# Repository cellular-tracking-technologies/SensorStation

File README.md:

# SensorStation

This repo contains the SensorStation schematics and CAD files. You can use this to assist with development, troubleshoot problems, or even create your own SensorStation.

If you are looking to purchased a fully assembled and tested SensorStation, complete with Raspberry Pi Compute module installed, visit: http://store.celltracktech.com/

# SensorStation Overview

The SensorStation is a powerful platform for transmitting and receiving information wirelessly, with multiple radio channels.

While its primary function is to collect data from wildlife telemetry devices, it can be used for any multi-channel wireless
application, including IoT, amateur radio, and building wireless networks.

The SensorStation offers the following features:

* Support for the Raspberry Pi Compute Module CM3+ (pre-programmed with SensorGnome if purchased from CTT)
* USB OTG switch allows for programming of Compute Module while directly connected to board
* GPS receiver with built in chip antenna, with RF switch for external antennas
* 5 radio channels with SMA connectors featuring the HopeRF footprint, making it compatible with VHF and UHF systems, such as LoRa or FSK, from 142-1000MHz and 2.4GHz
* Each radio is controlled by a dedicated Atmel AVR 32U4, featuring the Arduino bootloader, hardwired to the USB network
* Raspberry Pi compatible header for connecting accessories, such as the InkyPhat eInk screen and more
* 4 directional buttons
* 2 status indication LEDs controlled by GPIO
* 3 I2C accessory ports, with dedicated GPIO per port
* Multi-channel ADC, for measuring system voltages, temperature, light levels, battery voltage, solar voltage, and additional channels broken out
* DS3231 real time clock with extreme accuracy along with coin cell slot
* Composite video output
* Wide range DC power input from 8-24VDC
* 6 USB 2.0 ports, each with dedicated transaction translator, typically used for Software Defined Radio (SDR)
* SIM800C quad band GSM modem
* eSIM (SIM on chip), soldered on if purchased from CTT (requires data plan)

# SensorStation Acessories

Also available for a variety of SensorStation accessories. You can even build your own. Check our our SensorStation Acessory Template to learn more.

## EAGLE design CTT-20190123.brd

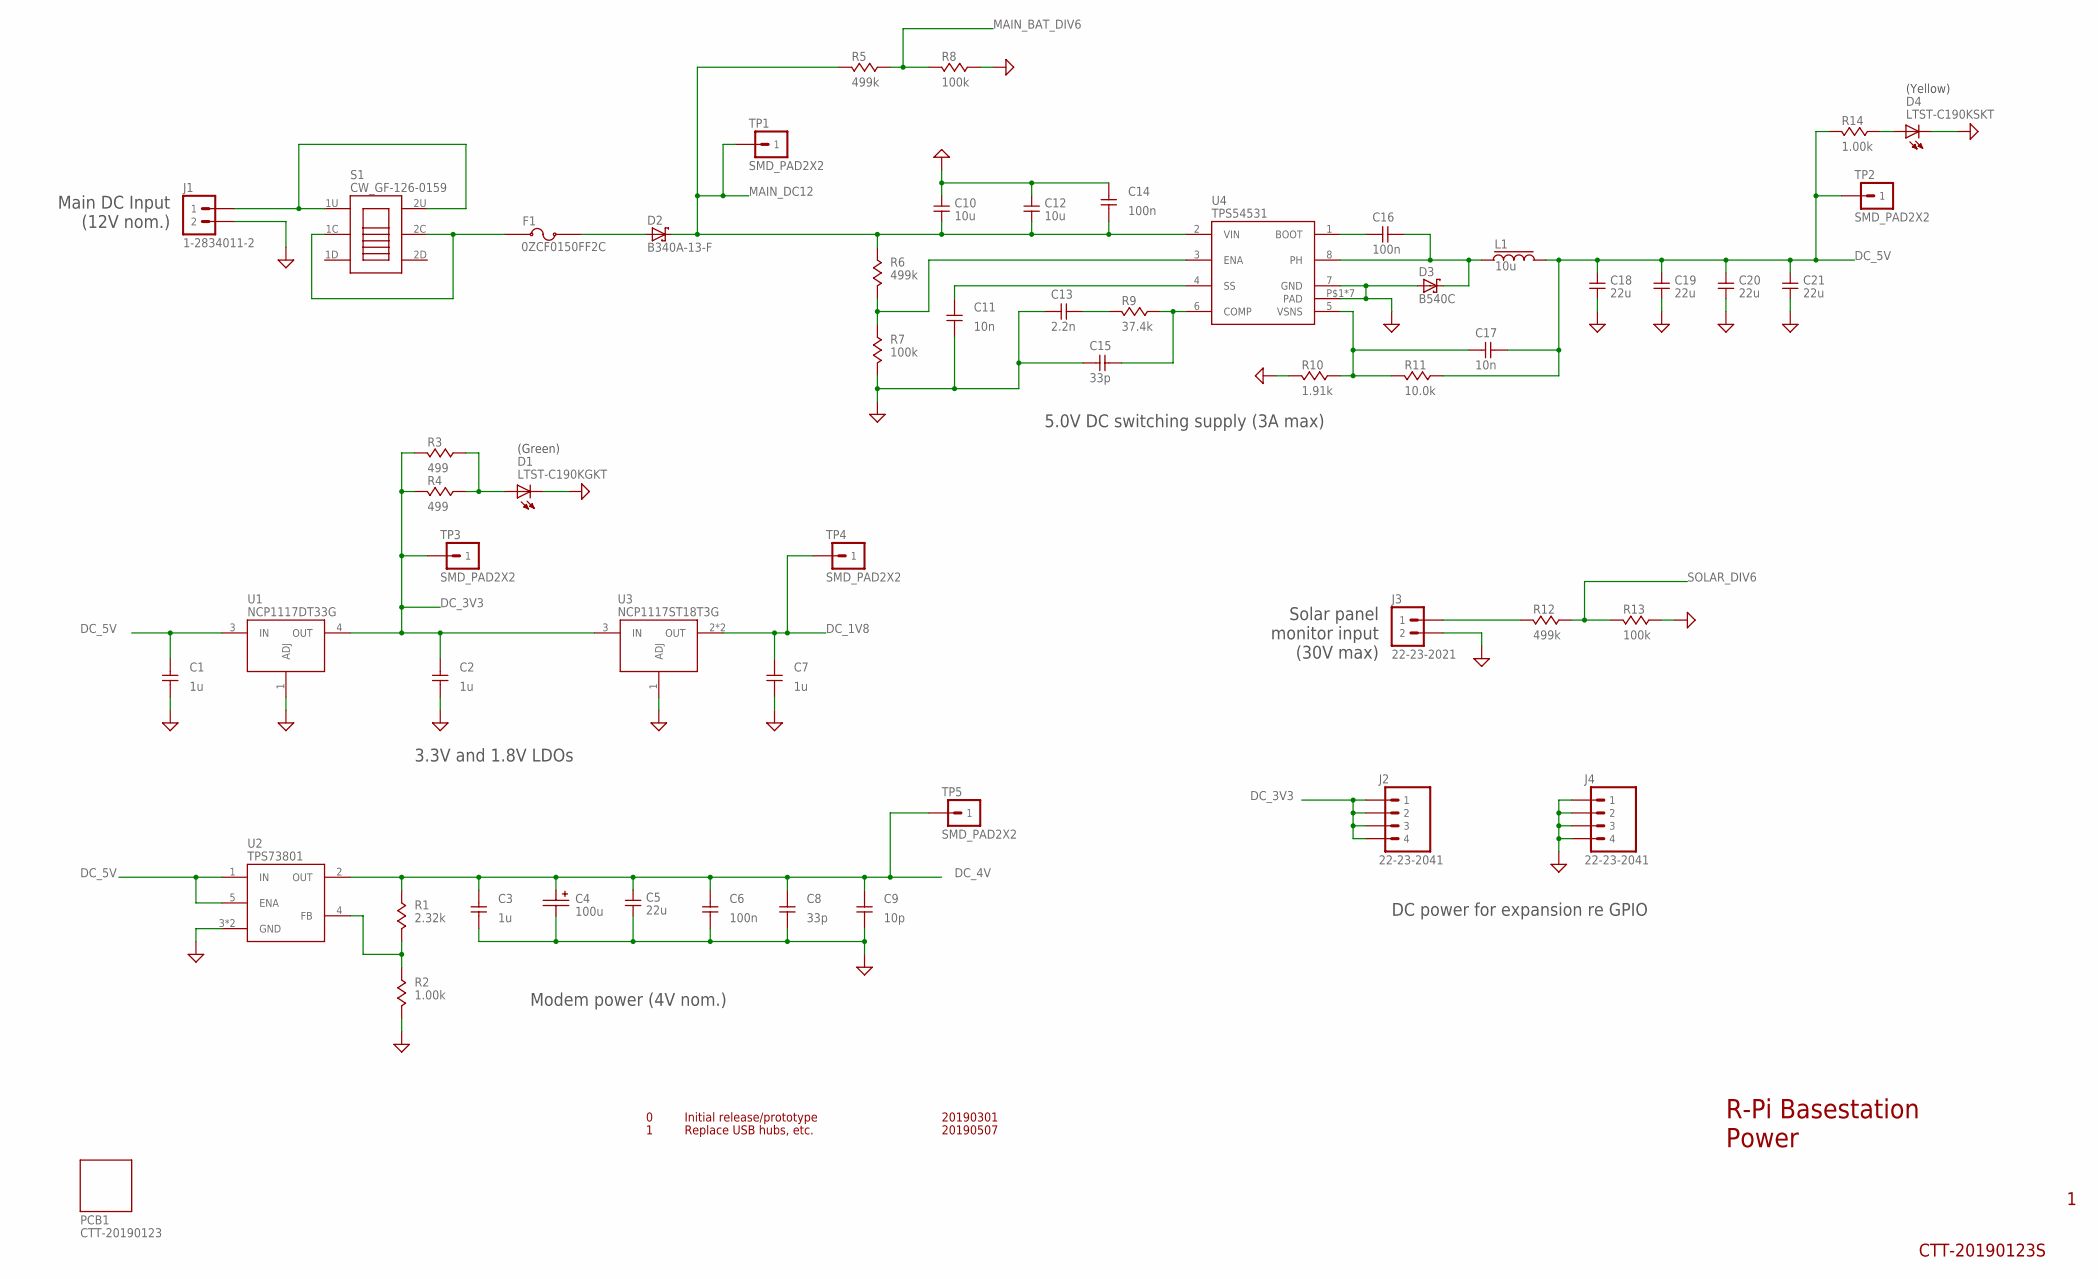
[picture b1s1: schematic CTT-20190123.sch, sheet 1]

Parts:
C1, C2, C3, C7: 1u; C0603_IPC7351_MED
C4: 100u; C7343
C5, C18, C19, C20, C21: 22u; C0805
C6, C14, C16: 100n; C0402_IPC7351_MED
C8, C15: 33p; C0402_IPC7351_MED
C9: 10p; C0402_IPC7351_MED
C10, C12: 10u; C0805
C11, C17: 10n; C0402_IPC7351_MED
C13: 2.2n; C0402_IPC7351_MED
D1: LTST-C190KGKT; LED0603
D2: B340A-13-F; SMA
D3: B540C; SMC
D4: LTST-C190KSKT; LED0603
F1: 0ZCF0150FF2C; SMD2920_0ZCF-SERIES
J1: 1-2834011-2
J2, J4: 22-23-2041; MTA100-4
J3: 22-23-2021; MTA100-2
L1: 10u; SRR1260
PCB1: CTT-20190123; BLANK_BRD
R1: 2.32k; R0402_IPC7351_MED
R2, R14: 1.00k; R0402_IPC7351_MED
R3, R4: 499; R0402_IPC7351_MED
R5, R6, R12: 499k; R0402_IPC7351_MED
R7, R8, R13: 100k; R0402_IPC7351_MED
R9: 37.4k; R0402_IPC7351_MED
R10: 1.91k; R0402_IPC7351_MED
R11: 10.0k; R0402_IPC7351_MED
S1: CW_GF-126-0159
TP1, TP2, TP3, TP4, TP5: SMD_PAD2X2; SMD_PAD
U1: NCP1117DT33G; DPAK
U2: TPS73801; TI_R-PDSO-G6
U3: NCP1117ST18T3G; SOT-223
U4: TPS54531; TI_R-PDSO-G8

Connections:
DC_1V8: C7.P$2 (2), TP4.1, U3.2 (OUT), U3.4 (OUT); also elsewhere on the board
DC_3V3: C2.P$2 (2), J2.1, J2.2, J2.3, J2.4, R3.P$2 (2), R4.P$2 (2), TP3.1, U1.4 (OUT), U3.3 (IN); also elsewhere on the board
DC_4V: C3.P$2 (2), C4.+ (POS), C5.2, C6.P$2 (2), C8.P$2 (2), C9.P$2 (2), R1.P$1 (1), TP5.1, U2.2 (OUT); also elsewhere on the board
DC_5V: C1.P$2 (2), C17.P$2 (2), C18.2, C19.2, C20.2, C21.2, L1.2, R11.P$1 (1), R14.P$2 (2), TP2.1, U1.3 (IN), U2.1 (IN), U2.5 (ENA); also elsewhere on the board
GND: C1.P$1 (1), C2.P$1 (1), C3.P$1 (1), C4.- (NEG), C5.1, C6.P$1 (1), C7.P$1 (1), C8.P$1 (1), C9.P$1 (1), C10.1, C11.P$1 (1), C12.1, C13.P$1 (1), C14.P$1 (1), C15.P$1 (1), C18.1, C19.1, C20.1, C21.1, D1.K, D3.A, D4.K, J1.2, J3.2, J4.1, J4.2, J4.3, J4.4, R2.P$2 (2), R7.P$2 (2), R8.P$1 (1), R10.P$2 (2), R13.P$1 (1), U1.1 (ADJ), U2.3 (GND), U2.TAB (GND), U3.1 (ADJ), U4.7 (GND), U4.P$1 (PAD), U4.P$2 (PAD), U4.P$3 (PAD), U4.P$4 (PAD), U4.P$5 (PAD), U4.P$6 (PAD), U4.PAD; also elsewhere on the board
MAIN_BAT_DIV6: R5.P$1 (1), R8.P$2 (2); also elsewhere on the board
MAIN_DC12: C10.2, C12.2, C14.P$2 (2), D2.C, R5.P$2 (2), R6.P$1 (1), TP1.1, U4.2 (VIN)
unnamed: C16.P$2 (2), D3.K (C), L1.P$1 (1), U4.8 (PH)
unnamed: R6.P$2 (2), R7.P$1 (1), U4.3 (ENA)
unnamed: C11.P$2 (2), U4.4 (SS)
unnamed: C16.P$1 (1), U4.1 (BOOT)
unnamed: C15.P$2 (2), R9.P$1 (1), U4.6 (COMP)
unnamed: C17.P$1 (1), R10.P$1 (1), R11.P$2 (2), U4.5 (VSNS)
unnamed: C13.P$2 (2), R9.P$2 (2)
unnamed: J1.1, S1.1U, S1.2U
unnamed: D2.A, F1.P$2
unnamed: D4.A, R14.P$1 (1)
unnamed: D1.A, R3.P$1 (1), R4.P$1 (1)
unnamed: R1.P$2 (2), R2.P$1 (1), U2.4 (FB)
unnamed: J3.1, R12.P$2 (2)
unnamed: F1.P$1, S1.1C, S1.2C
SOLAR_DIV6: R12.P$1 (1), R13.P$2 (2); also elsewhere on the board

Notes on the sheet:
Main DC Input (12V nom.)
Modem power (4V nom.)
Solar panel monitor input (30V max)
5.0V DC switching supply (3A max)
3.3V and 1.8V LDOs
DC power for expansion re GPIO
R-Pi Basestation Power
CTT-20190123S
(Yellow)
(Green)
20190507
Initial release/prototype
Replace USB hubs, etc.
20190301

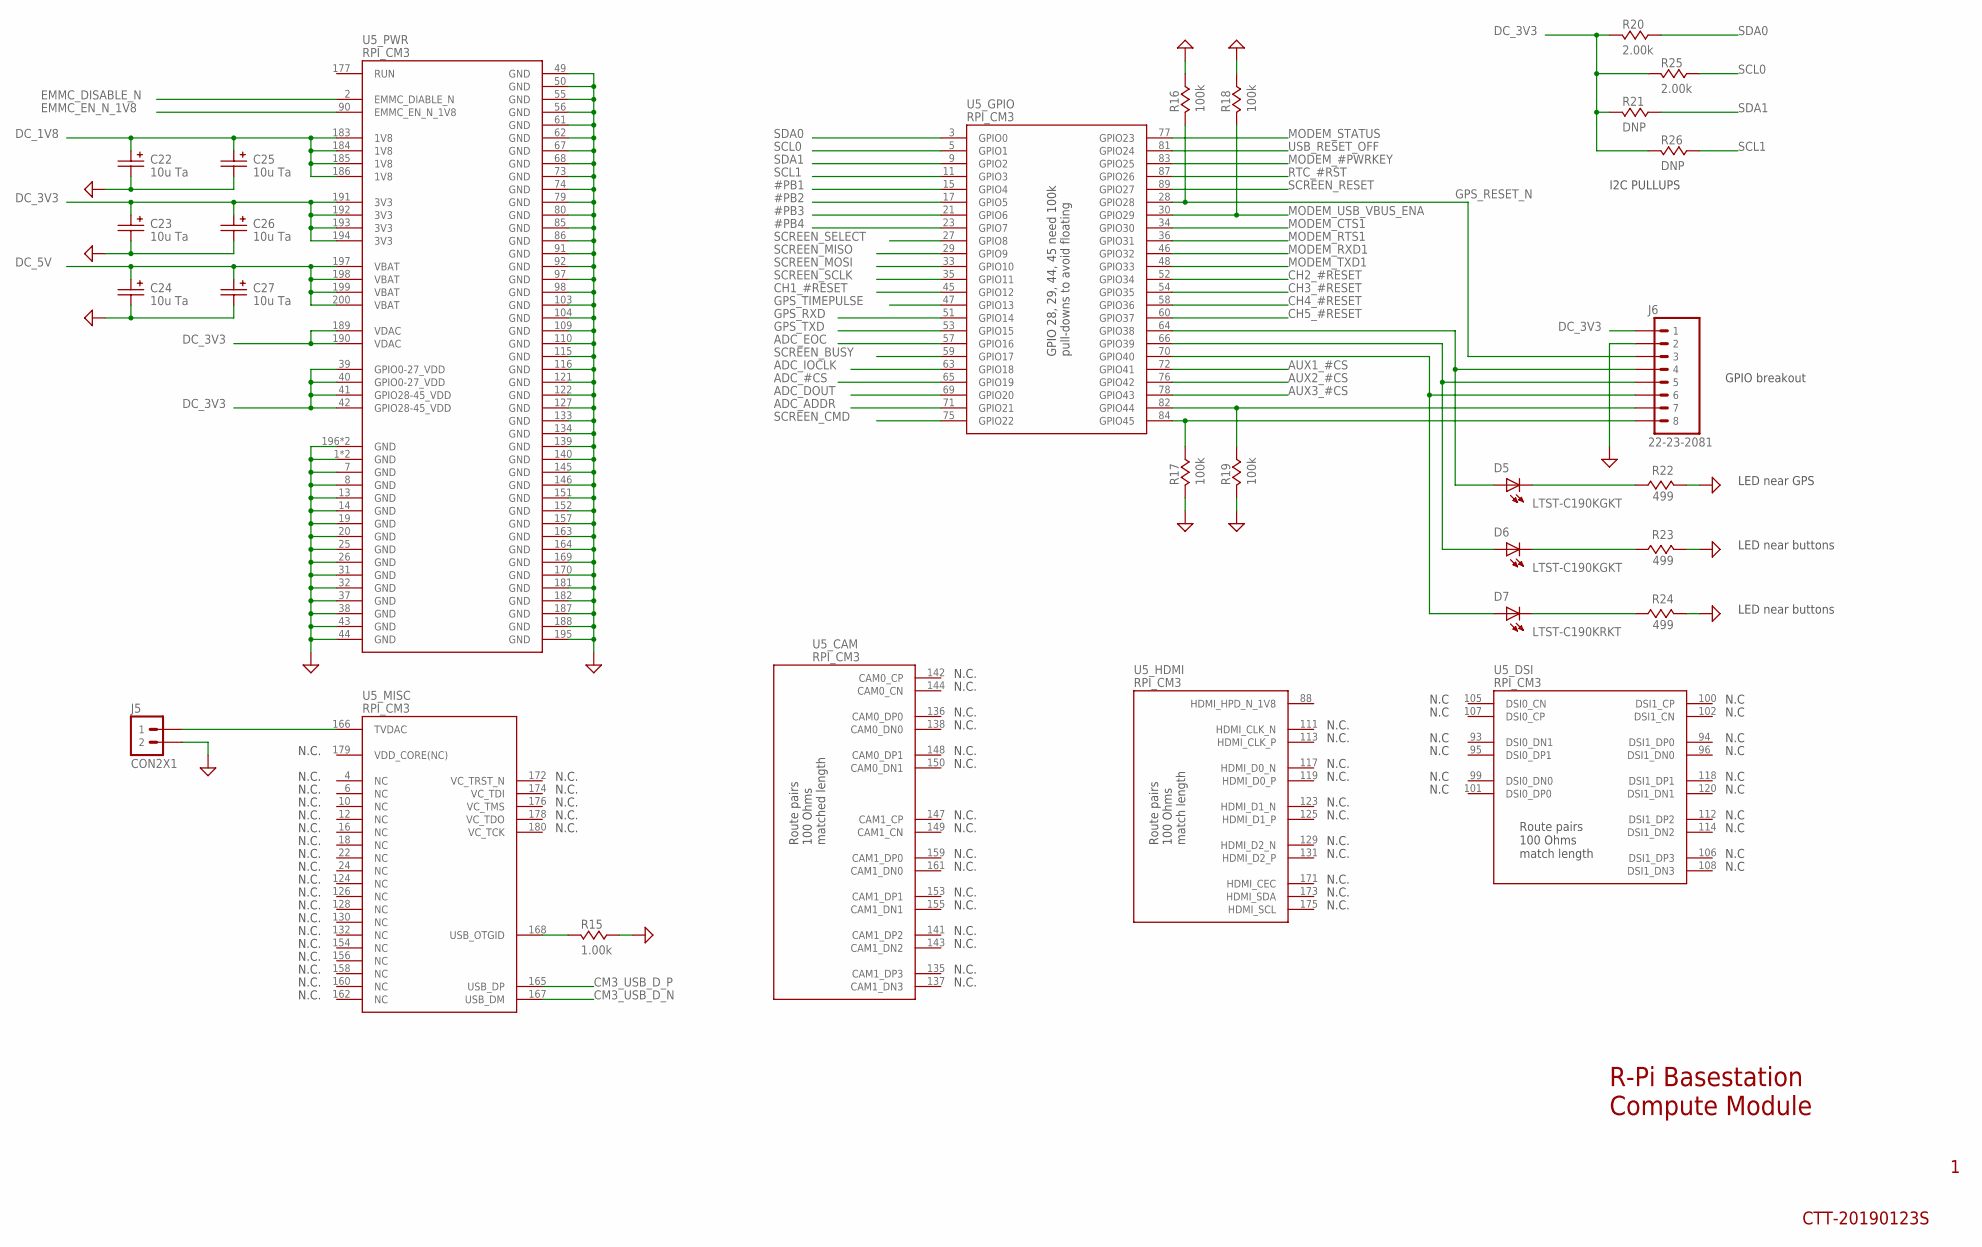
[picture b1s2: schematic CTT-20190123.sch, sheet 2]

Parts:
C22, C23, C24, C25, C26, C27: 10u Ta; CAP1411-AVX_F97SERIES
D5, D6: LTST-C190KGKT; LED0603
D7: LTST-C190KRKT; LED0603
J5: CON2X1
J6: 22-23-2081; MTA100-8
R15: 1.00k; R0402_IPC7351_MED
R16, R17, R18, R19: 100k; R0402_IPC7351_MED
R20, R25: 2.00k; R0402_IPC7351_MED
R21, R26: DNP; R0402_IPC7351_MED
R22, R23, R24: 499; R0402_IPC7351_MED
U5: RPI_CM3; 1473149-4

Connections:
#PB1: U5.15 (GPIO4); also elsewhere on the board
#PB2: U5.17 (GPIO5); also elsewhere on the board
#PB3: U5.21 (GPIO6); also elsewhere on the board
#PB4: U5.23 (GPIO7); also elsewhere on the board
ADC_#CS: U5.65 (GPIO19); also elsewhere on the board
ADC_ADDR: U5.71 (GPIO21); also elsewhere on the board
ADC_DOUT: U5.69 (GPIO20); also elsewhere on the board
ADC_EOC: U5.57 (GPIO16); also elsewhere on the board
ADC_IOCLK: U5.63 (GPIO18); also elsewhere on the board
AUX1_#CS: U5.72 (GPIO41); also elsewhere on the board
AUX2_#CS: U5.76 (GPIO42); also elsewhere on the board
AUX3_#CS: U5.78 (GPIO43); also elsewhere on the board
CH1_#RESET: U5.45 (GPIO12); also elsewhere on the board
CH2_#RESET: U5.52 (GPIO34); also elsewhere on the board
CH3_#RESET: U5.54 (GPIO35); also elsewhere on the board
CH4_#RESET: U5.58 (GPIO36); also elsewhere on the board
CH5_#RESET: U5.60 (GPIO37); also elsewhere on the board
CM3_USB_D_N: U5.167 (USB_DM); also elsewhere on the board
CM3_USB_D_P: U5.165 (USB_DP); also elsewhere on the board
DC_1V8: C22.+ (POS), C25.+ (POS), U5.183 (1V8), U5.184 (1V8), U5.185 (1V8), U5.186 (1V8); also elsewhere on the board
DC_3V3: C23.+ (POS), C26.+ (POS), J6.1, R20.P$2 (2), R21.P$2 (2), R25.P$2 (2), R26.P$2 (2), U5.39 (GPIO0-27_VDD), U5.40 (GPIO0-27_VDD), U5.41 (GPIO28-45_VDD), U5.42 (GPIO28-45_VDD), U5.189 (VDAC), U5.190 (VDAC), U5.191 (3V3), U5.192 (3V3), U5.193 (3V3), U5.194 (3V3); also elsewhere on the board
DC_5V: C24.+ (POS), C27.+ (POS), U5.197 (VBAT), U5.198 (VBAT), U5.199 (VBAT), U5.200 (VBAT); also elsewhere on the board
EMMC_DISABLE_N: U5.2 (EMMC_DIABLE_N); also elsewhere on the board
EMMC_EN_N_1V8: U5.90 (EMMC_EN_N_1V8); also elsewhere on the board
GND: C22.- (NEG), C23.- (NEG), C24.- (NEG), C25.- (NEG), C26.- (NEG), C27.- (NEG), J5.2, J6.2, R15.P$1 (1), R16.P$1 (1), R17.P$2 (2), R18.P$1 (1), R19.P$2 (2), R22.P$2 (2), R23.P$2 (2), R24.P$2 (2), U5.1 (GND), U5.7 (GND), U5.8 (GND), U5.13 (GND), U5.14 (GND), U5.19 (GND), U5.20 (GND), U5.25 (GND), U5.26 (GND), U5.31 (GND), U5.32 (GND), U5.37 (GND), U5.38 (GND), U5.43 (GND), U5.44 (GND), U5.49 (GND), U5.50 (GND), U5.55 (GND), U5.56 (GND), U5.61 (GND), U5.62 (GND), U5.67 (GND), U5.68 (GND), U5.73 (GND), U5.74 (GND), U5.79 (GND), U5.80 (GND), U5.85 (GND), U5.86 (GND), U5.91 (GND), U5.92 (GND), U5.97 (GND), U5.98 (GND), U5.103 (GND), U5.104 (GND), U5.109 (GND), U5.110 (GND), U5.115 (GND), U5.116 (GND), U5.121 (GND), U5.122 (GND), U5.127 (GND), U5.133 (GND), U5.134 (GND), U5.139 (GND), U5.140 (GND), U5.145 (GND), U5.146 (GND), U5.151 (GND), U5.152 (GND), U5.157 (GND), U5.163 (GND), U5.164 (GND), U5.169 (GND), U5.170 (GND), U5.181 (GND), U5.182 (GND), U5.187 (GND), U5.188 (GND), U5.195 (GND), U5.196 (GND), U5.P$1 (GND), U5.P$2 (GND); also elsewhere on the board
GPS_RESET_N: J6.3, R16.P$2 (2), U5.28 (GPIO28); also elsewhere on the board
GPS_RXD: U5.51 (GPIO14); also elsewhere on the board
GPS_TIMEPULSE: U5.47 (GPIO13); also elsewhere on the board
GPS_TXD: U5.53 (GPIO15); also elsewhere on the board
MODEM_#PWRKEY: U5.83 (GPIO25); also elsewhere on the board
MODEM_CTS1: U5.34 (GPIO30); also elsewhere on the board
MODEM_RTS1: U5.36 (GPIO31); also elsewhere on the board
MODEM_RXD1: U5.46 (GPIO32); also elsewhere on the board
MODEM_STATUS: U5.77 (GPIO23); also elsewhere on the board
MODEM_TXD1: U5.48 (GPIO33); also elsewhere on the board
MODEM_USB_VBUS_ENA: R18.P$2 (2), U5.30 (GPIO29); also elsewhere on the board
unnamed: J5.1, U5.166 (TVDAC)
unnamed: R15.P$2 (2), U5.168 (USB_OTGID)
unnamed: J6.8, R17.P$1 (1), U5.84 (GPIO45)
unnamed: J6.7, R19.P$1 (1), U5.82 (GPIO44)
unnamed: D5.A, J6.4, U5.64 (GPIO38)
unnamed: D6.A, J6.5, U5.66 (GPIO39)
unnamed: D7.A, J6.6, U5.70 (GPIO40)
unnamed: D6.K, R23.P$1 (1)
unnamed: D7.K, R24.P$1 (1)
unnamed: D5.K, R22.P$1 (1)
RTC_#RST: U5.87 (GPIO26); also elsewhere on the board
SCL0: R25.P$1 (1), U5.5 (GPIO1); also elsewhere on the board
SCL1: R26.P$1 (1), U5.11 (GPIO3); also elsewhere on the board
SCREEN_BUSY: U5.59 (GPIO17); also elsewhere on the board
SCREEN_CMD: U5.75 (GPIO22); also elsewhere on the board
SCREEN_MISO: U5.29 (GPIO9); also elsewhere on the board
SCREEN_MOSI: U5.33 (GPIO10); also elsewhere on the board
SCREEN_RESET: U5.89 (GPIO27); also elsewhere on the board
SCREEN_SCLK: U5.35 (GPIO11); also elsewhere on the board
SCREEN_SELECT: U5.27 (GPIO8); also elsewhere on the board
SDA0: R20.P$1 (1), U5.3 (GPIO0); also elsewhere on the board
SDA1: R21.P$1 (1), U5.9 (GPIO2); also elsewhere on the board
USB_RESET_OFF: U5.81 (GPIO24); also elsewhere on the board

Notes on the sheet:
N.C.
N.C
I2C PULLUPS
R-Pi Basestation Compute Module
CTT-20190123S
GPIO breakout
LED near GPS
LED near buttons

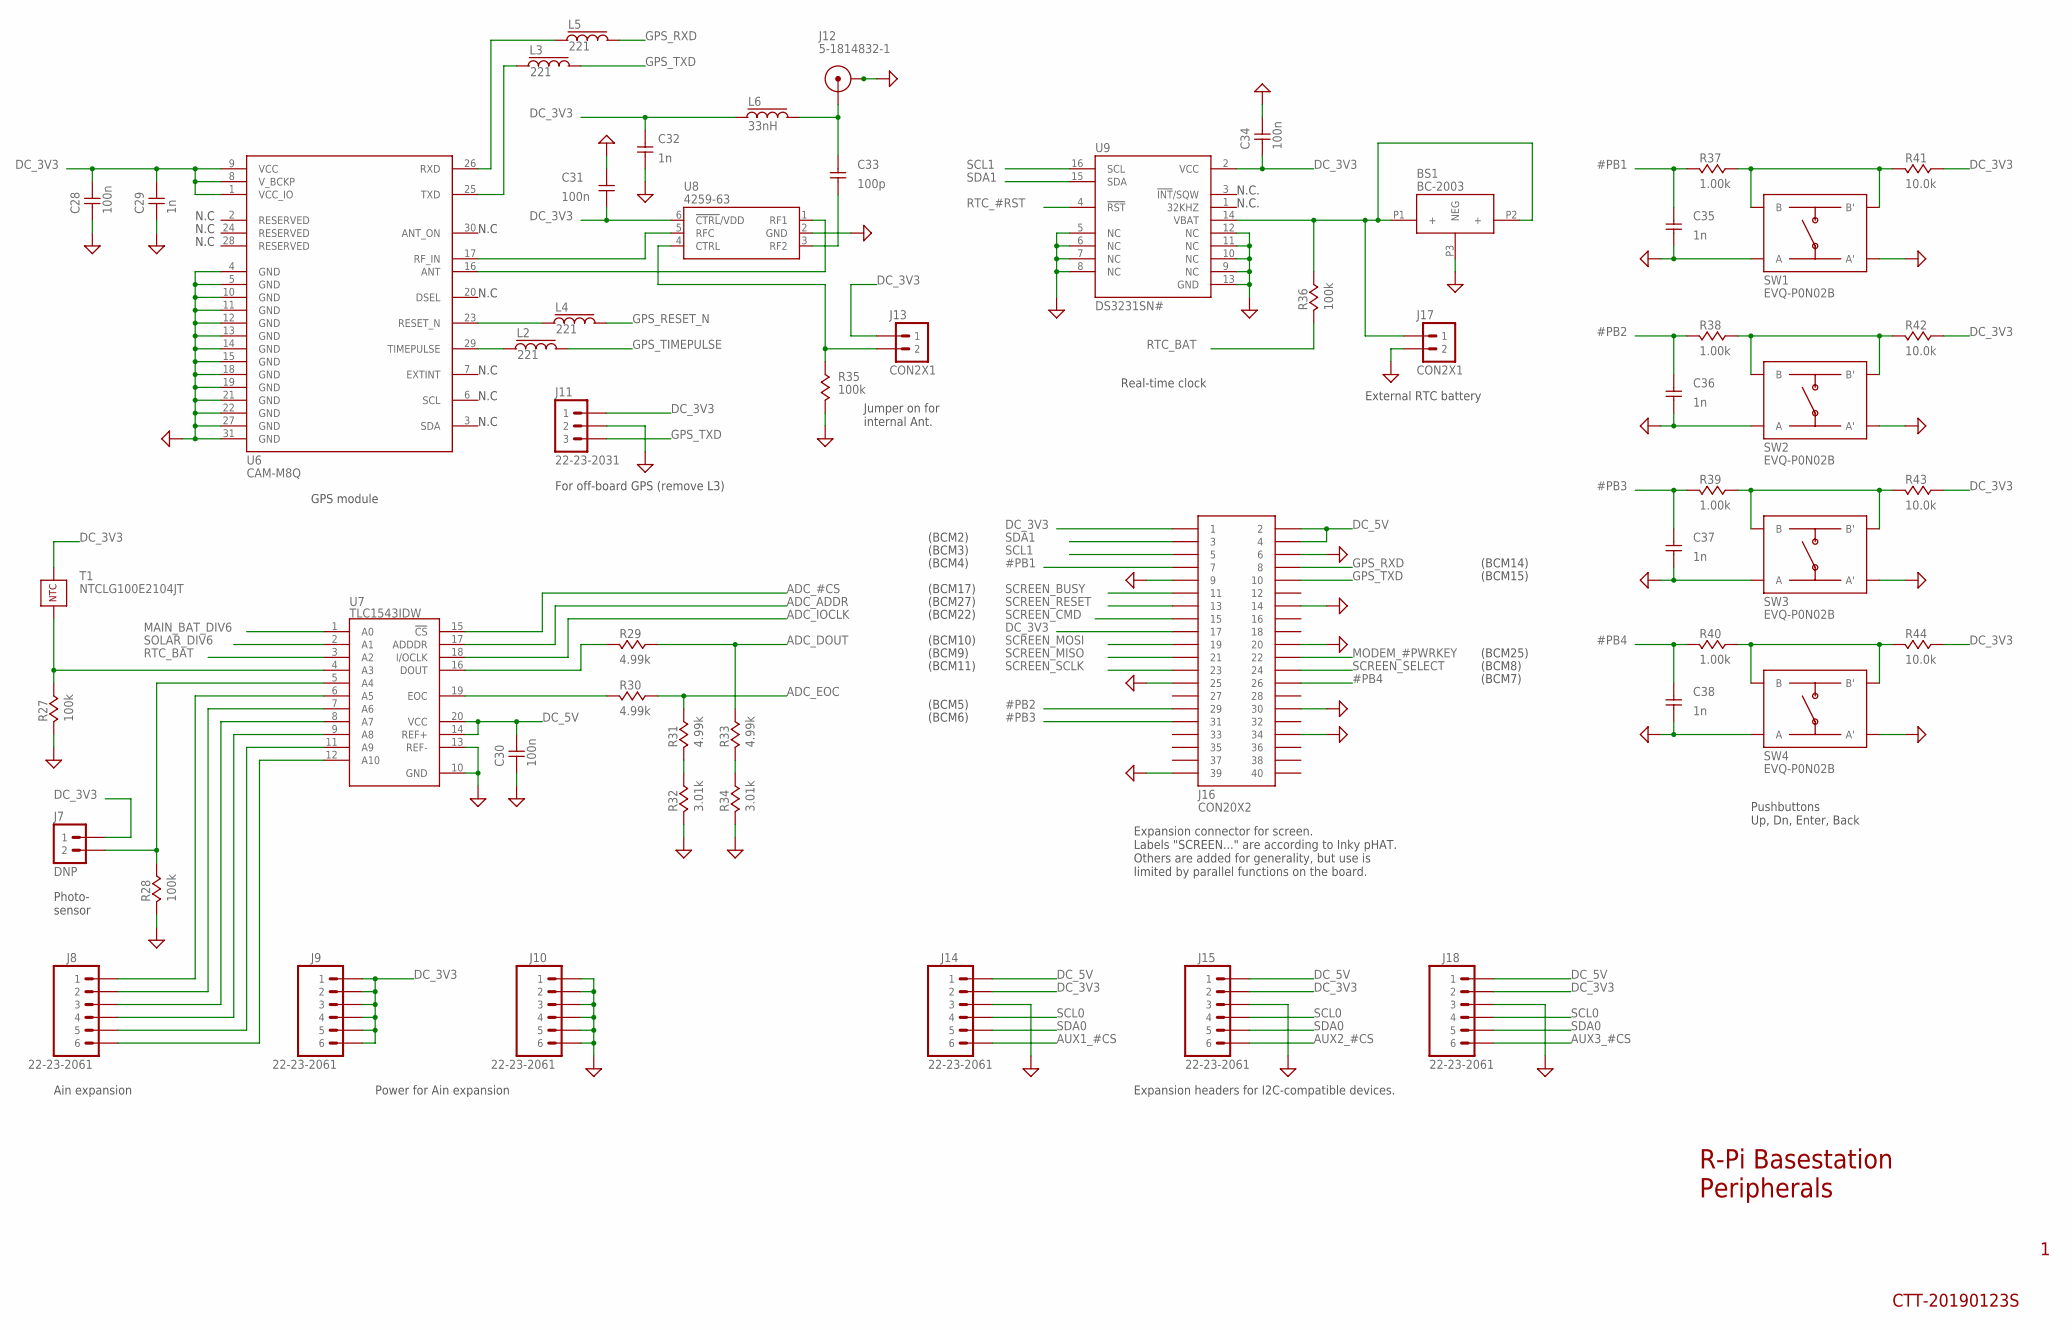
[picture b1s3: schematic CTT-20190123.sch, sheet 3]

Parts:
BS1: BC-2003; BC-2003-TR
C28, C30, C31, C34: 100n; C0402_IPC7351_MED
C29, C32, C35, C36, C37, C38: 1n; C0402_IPC7351_MED
C33: 100p; C0402_IPC7351_MED
J7: DNP; CON2X1
J8, J9, J10, J14, J15, J18: 22-23-2061; MTA100-6
J11: 22-23-2031; MTA100-3
J12: 5-1814832-1; CON_SMA_TH_VERT
J13, J17: CON2X1
J16: CON20X2
L2, L3, L4, L5: 221; L0402_IPC7351_MED
L6: 33nH; L0402_IPC7351_MED
R27, R28, R35, R36: 100k; R0402_IPC7351_MED
R29, R30, R31, R33: 4.99k; R0402_IPC7351_MED
R32, R34: 3.01k; R0402_IPC7351_MED
R37, R38, R39, R40: 1.00k; R0402_IPC7351_MED
R41, R42, R43, R44: 10.0k; R0402_IPC7351_MED
SW1, SW2, SW3, SW4: EVQ-P0N02B; EVQP0
T1: NTCLG100E2104JT; DO35-VERT
U6: CAM-M8Q; LCC31
U7: TLC1543IDW; SOIC20_DW0020A
U8: 4259-63; SC-70_PEREGRINE
U9: DS3231SN#; SO16-WIDE_MAXIM

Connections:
#PB1: C35.P$2 (2), J16.7, R37.P$2 (2); also elsewhere on the board
#PB2: C36.P$2 (2), J16.29, R38.P$2 (2); also elsewhere on the board
#PB3: C37.P$2 (2), J16.31, R39.P$2 (2); also elsewhere on the board
#PB4: C38.P$2 (2), J16.26, R40.P$2 (2); also elsewhere on the board
ADC_#CS: U7.15 (!CS); also elsewhere on the board
ADC_ADDR: U7.17 (ADDDR); also elsewhere on the board
ADC_DOUT: R29.P$1 (1), R33.P$1 (1); also elsewhere on the board
ADC_EOC: R30.P$1 (1), R31.P$1 (1); also elsewhere on the board
ADC_IOCLK: U7.18 (I/OCLK); also elsewhere on the board
AUX1_#CS: J14.6; also elsewhere on the board
AUX2_#CS: J15.6; also elsewhere on the board
AUX3_#CS: J18.6; also elsewhere on the board
DC_3V3: C28.P$2 (2), C29.P$2 (2), C31.P$1 (1), C32.P$2 (2), C34.P$1 (1), J7.1, J9.1, J9.2, J9.3, J9.4, J9.5, J9.6, J11.1, J13.1, J14.2, J15.2, J16.1, J16.17, J18.2, L6.P$1 (1), R41.P$1 (1), R42.P$1 (1), R43.P$1 (1), R44.P$1 (1), T1.P$1 (1), U6.1 (VCC_IO), U6.8 (V_BCKP), U6.9 (VCC), U8.6 (!CTRL!/VDD), U9.2 (VCC); also elsewhere on the board
DC_5V: C30.P$2 (2), J14.1, J15.1, J16.2, J16.4, J18.1, U7.14 (REF+), U7.20 (VCC); also elsewhere on the board
GND: BS1.P3 (NEG), C28.P$1 (1), C29.P$1 (1), C30.P$1 (1), C31.P$2 (2), C32.P$1 (1), C34.P$2 (2), C35.P$1 (1), C36.P$1 (1), C37.P$1 (1), C38.P$1 (1), J10.1, J10.2, J10.3, J10.4, J10.5, J10.6, J11.2, J12.P$1 (GND), J12.P$2 (GND), J12.P$3 (GND), J12.P$4 (GND), J14.3, J15.3, J16.6, J16.9, J16.14, J16.20, J16.25, J16.30, J16.34, J16.39, J17.2, J18.3, R27.P$2 (2), R28.P$2 (2), R32.P$2 (2), R34.P$2 (2), R35.P$2 (2), SW1.A, SW1.A@1 (A'), SW2.A, SW2.A@1 (A'), SW3.A, SW3.A@1 (A'), SW4.A, SW4.A@1 (A'), U6.4 (GND), U6.5 (GND), U6.10 (GND), U6.11 (GND), U6.12 (GND), U6.13 (GND), U6.14 (GND), U6.15 (GND), U6.18 (GND), U6.19 (GND), U6.21 (GND), U6.22 (GND), U6.27 (GND), U6.31 (GND), U7.10 (GND), U7.13 (REF-), U8.2 (GND), U9.5 (NC), U9.6 (NC), U9.7 (NC), U9.8 (NC), U9.9 (NC), U9.10 (NC), U9.11 (NC), U9.12 (NC), U9.13 (GND); also elsewhere on the board
GPS_RESET_N: L4.P$2 (2); also elsewhere on the board
GPS_RXD: J16.8, L5.P$2 (2); also elsewhere on the board
GPS_TIMEPULSE: L2.P$2 (2); also elsewhere on the board
GPS_TXD: J11.3, J16.10, L3.P$2 (2); also elsewhere on the board
MAIN_BAT_DIV6: U7.1 (A0); also elsewhere on the board
MODEM_#PWRKEY: J16.22; also elsewhere on the board
unnamed: C33.P$2 (2), J12.C (SIG), L6.P$2 (2)
unnamed: U6.17 (RF_IN), U8.5 (RFC)
unnamed: C33.P$1 (1), U8.3 (RF2)
unnamed: U6.16 (ANT), U8.1 (RF1)
unnamed: L4.P$1 (1), U6.23 (RESET_N)
unnamed: L5.P$1 (1), U6.26 (RXD)
unnamed: L3.P$1 (1), U6.25 (TXD)
unnamed: L2.P$1 (1), U6.29 (TIMEPULSE)
unnamed: BS1.P1 (+), BS1.P2 (+), J17.1, R36.P$1 (1), U9.14 (VBAT)
unnamed: R30.P$2 (2), U7.19 (EOC)
unnamed: R29.P$2 (2), U7.16 (DOUT)
unnamed: J7.2, R28.P$1 (1), U7.5 (A4)
unnamed: R31.P$2 (2), R32.P$1 (1)
unnamed: R33.P$2 (2), R34.P$1 (1)
unnamed: R27.P$1 (1), T1.P$2 (2), U7.4 (A3)
unnamed: J8.1, U7.6 (A5)
unnamed: J8.2, U7.7 (A6)
unnamed: J8.3, U7.8 (A7)
unnamed: J8.4, U7.9 (A8)
unnamed: J8.5, U7.11 (A9)
unnamed: J8.6, U7.12 (A10)
unnamed: R40.P$1 (1), R44.P$2 (2), SW4.B, SW4.B@1 (B')
unnamed: R39.P$1 (1), R43.P$2 (2), SW3.B, SW3.B@1 (B')
unnamed: R38.P$1 (1), R42.P$2 (2), SW2.B, SW2.B@1 (B')
unnamed: R37.P$1 (1), R41.P$2 (2), SW1.B, SW1.B@1 (B')
unnamed: J13.2, R35.P$1 (1), U8.4 (CTRL)
RTC_#RST: U9.4 (!RST); also elsewhere on the board
RTC_BAT: R36.P$2 (2), U7.3 (A2)
SCL0: J14.4, J15.4, J18.4; also elsewhere on the board
SCL1: J16.5, U9.16 (SCL); also elsewhere on the board
SCREEN_BUSY: J16.11; also elsewhere on the board
SCREEN_CMD: J16.15; also elsewhere on the board
SCREEN_MISO: J16.21; also elsewhere on the board
SCREEN_MOSI: J16.19; also elsewhere on the board
SCREEN_RESET: J16.13; also elsewhere on the board
SCREEN_SCLK: J16.23; also elsewhere on the board
SCREEN_SELECT: J16.24; also elsewhere on the board
SDA0: J14.5, J15.5, J18.5; also elsewhere on the board
SDA1: J16.3, U9.15 (SDA); also elsewhere on the board
SOLAR_DIV6: U7.2 (A1); also elsewhere on the board

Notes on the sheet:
N.C
N.C.
(BCM17)
(BCM27)
(BCM22)
(BCM10)
(BCM11)
(BCM8)
Expansion connector for screen. Labels "SCREEN..." are according to Inky pHAT. Others are added for generality, but use is limited by parallel functions on the board.
Expansion headers for I2C-compatible devices.
Photo- sensor
Ain expansion
Power for Ain expansion
For off-board GPS (remove L3)
GPS module
Real-time clock
External RTC battery
Pushbuttons Up, Dn, Enter, Back
R-Pi Basestation Peripherals
CTT-20190123S
(BCM4)
(BCM9)
(BCM5)
(BCM6)
(BCM7)
(BCM25)
(BCM15)
(BCM14)
Jumper on for internal Ant.
(BCM2)
(BCM3)

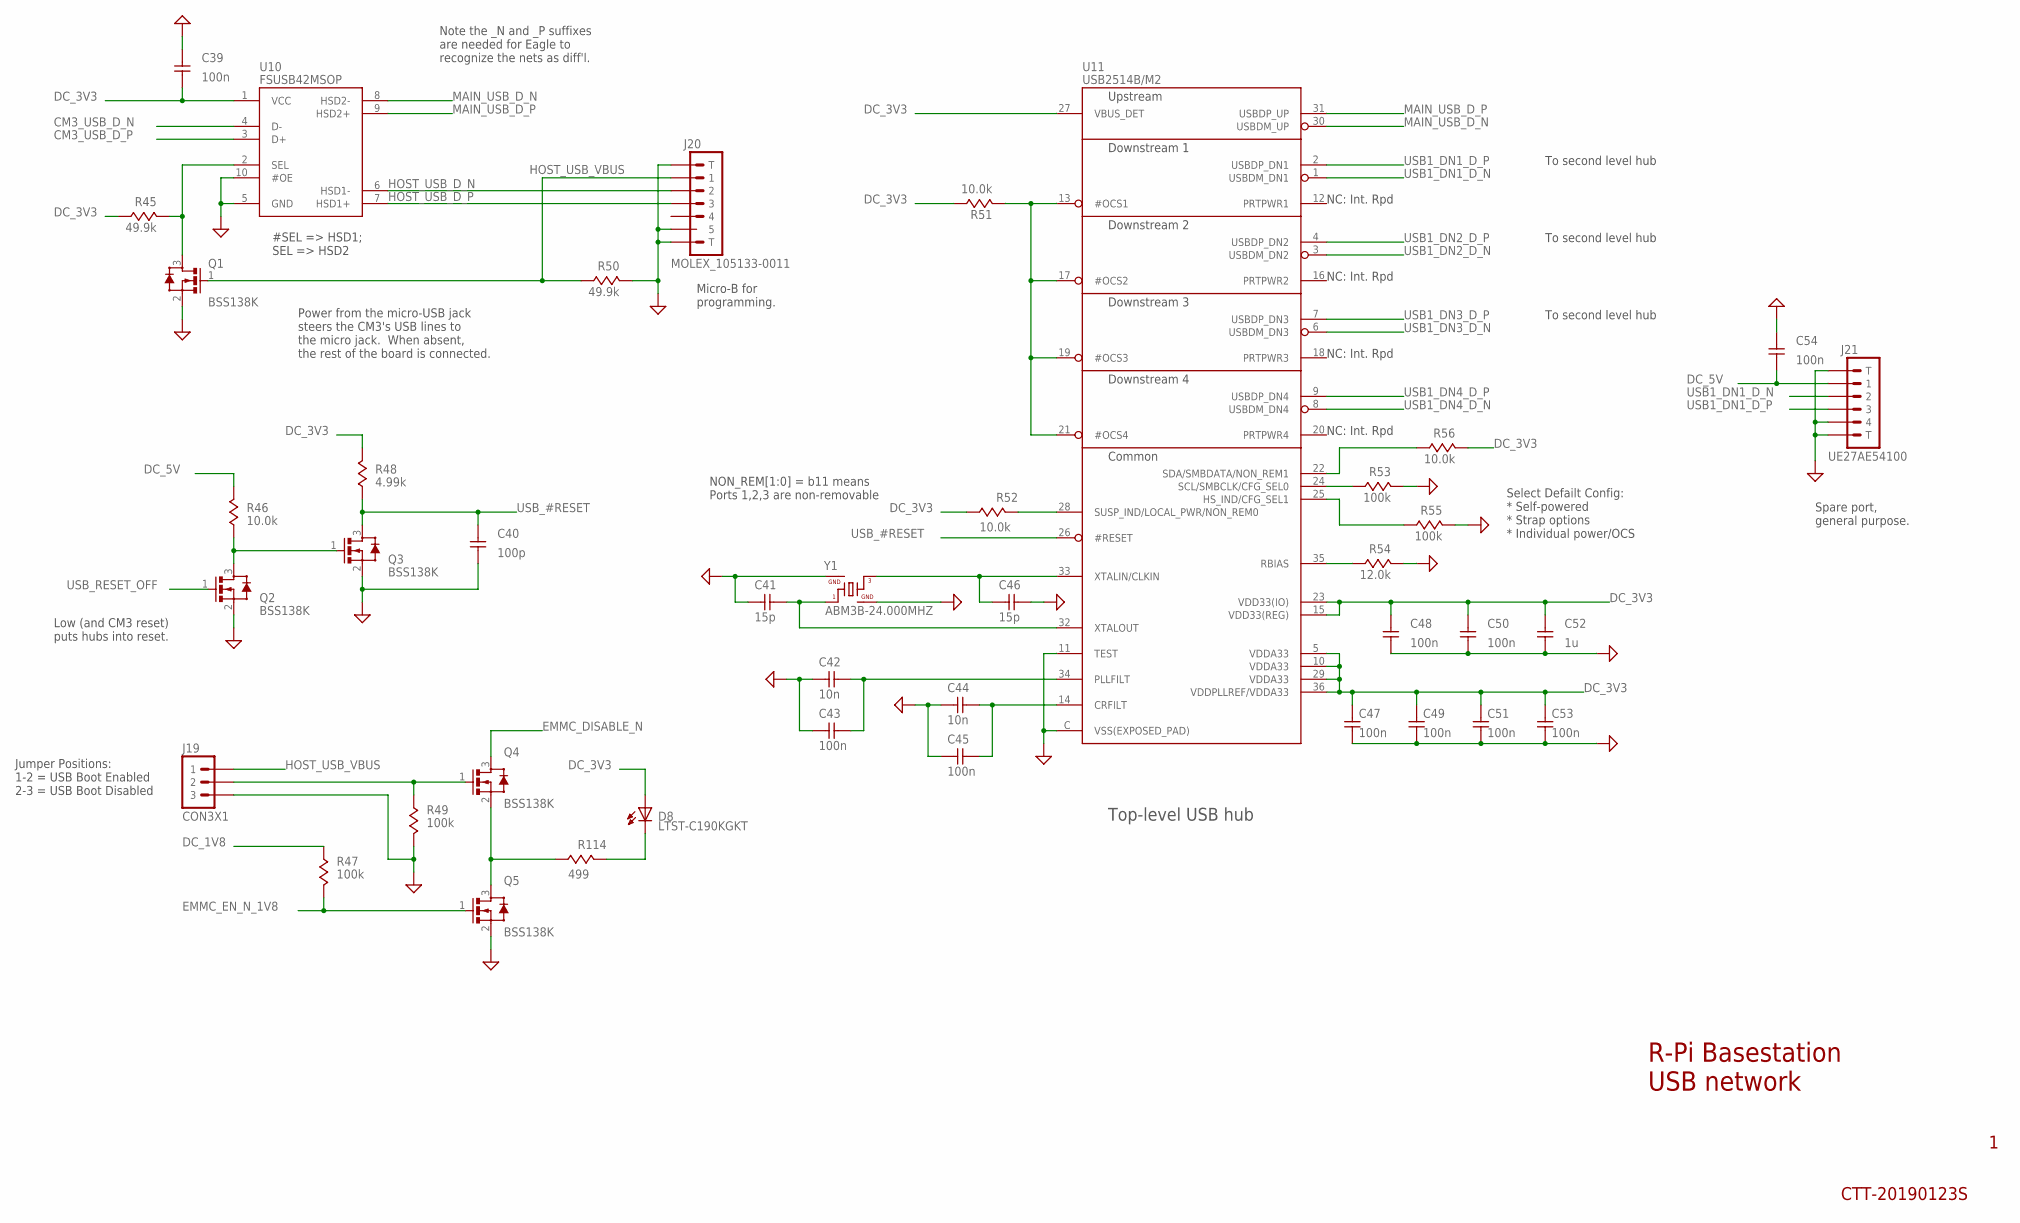
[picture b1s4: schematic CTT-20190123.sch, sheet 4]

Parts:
C39, C43, C45, C47, C48, C49, C50, C51, C53, C54: 100n; C0402_IPC7351_MED
C40: 100p; C0402_IPC7351_MED
C41, C46: 15p; C0402_IPC7351_MED
C42, C44: 10n; C0402_IPC7351_MED
C52: 1u; C0603_IPC7351_MED
D8: LTST-C190KGKT; LED0603
J19: CON3X1
J20: MOLEX_105133-0011
J21: UE27AE54100
Q1, Q2, Q3, Q4, Q5: BSS138K; SOT-23
R45, R50: 49.9k; R0402_IPC7351_MED
R46, R51, R52, R56: 10.0k; R0402_IPC7351_MED
R47, R49, R53, R55: 100k; R0402_IPC7351_MED
R48: 4.99k; R0402_IPC7351_MED
R54: 12.0k; R0402_IPC7351_MED
R114: 499; R0402_IPC7351_MED
U10: FSUSB42MSOP; MSOP-10
U11: USB2514B/M2; SQFN-36
Y1: ABM3B-24.000MHZ; ABM3B

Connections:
CM3_USB_D_N: U10.4 (D-); also elsewhere on the board
CM3_USB_D_P: U10.3 (D+); also elsewhere on the board
DC_1V8: R47.P$1 (1); also elsewhere on the board
DC_3V3: C39.P$1 (1), C47.P$2 (2), C48.P$2 (2), C49.P$2 (2), C50.P$2 (2), C51.P$2 (2), C52.P$2 (2), C53.P$2 (2), D8.A, R45.P$1 (1), R48.P$2 (2), R51.P$1 (1), R52.P$1 (1), R56.P$2 (2), U10.1 (VCC), U11.5 (VDDA33), U11.10 (VDDA33), U11.15 (VDD33(REG)), U11.23 (VDD33(IO)), U11.27 (VBUS_DET), U11.29 (VDDA33), U11.36 (VDDPLLREF/VDDA33); also elsewhere on the board
DC_5V: C54.P$1 (1), J21.1, R46.P$2 (2); also elsewhere on the board
EMMC_DISABLE_N: Q4.3 (D); also elsewhere on the board
EMMC_EN_N_1V8: Q5.1 (G), R47.P$2 (2); also elsewhere on the board
GND: C39.P$2 (2), C40.P$1 (1), C41.P$1 (1), C42.P$1 (1), C43.P$1 (1), C44.P$1 (1), C45.P$1 (1), C46.P$2 (2), C47.P$1 (1), C48.P$1 (1), C49.P$1 (1), C50.P$1 (1), C51.P$1 (1), C52.P$1 (1), C53.P$1 (1), C54.P$2 (2), J19.3, J20.5, J20.P$1 (T), J20.P$2 (T), J20.P$3 (T), J21.4, J21.P$1 (T), J21.P$2 (T), Q1.2 (S), Q2.2 (S), Q3.2 (S), Q5.2 (S), R49.P$2 (2), R50.P$2 (2), R53.P$2 (2), R54.P$2 (2), R55.P$2 (2), U10.5 (GND), U10.10 (#OE), U11.11 (TEST), U11.C (VSS(EXPOSED_PAD)), Y1.2, Y1.4; also elsewhere on the board
HOST_USB_D_N: J20.2, U10.6 (HSD1-)
HOST_USB_D_P: J20.3, U10.7 (HSD1+)
HOST_USB_VBUS: J19.1, J20.1, Q1.1 (G), R50.P$1 (1)
MAIN_USB_D_N: U10.8 (HSD2-), U11.30 (USBDM_UP)
MAIN_USB_D_P: U10.9 (HSD2+), U11.31 (USBDP_UP)
unnamed: Q4.2 (S), Q5.3 (D), R114.P$1 (1)
unnamed: J19.2, Q4.1 (G), R49.P$1 (1)
unnamed: D8.K, R114.P$2 (2)
unnamed: Q1.3 (D), R45.P$2 (2), U10.2 (SEL)
unnamed: C46.P$1 (1), U11.33 (XTALIN/CLKIN), Y1.3
unnamed: C41.P$2 (2), U11.32 (XTALOUT), Y1.1
unnamed: R53.P$1 (1), U11.24 (SCL/SMBCLK/CFG_SEL0)
unnamed: C42.P$2 (2), C43.P$2 (2), U11.34 (PLLFILT)
unnamed: C44.P$2 (2), C45.P$2 (2), U11.14 (CRFILT)
unnamed: R55.P$1 (1), U11.25 (HS_IND/CFG_SEL1)
unnamed: R54.P$1 (1), U11.35 (RBIAS)
unnamed: R51.P$2 (2), U11.13 (#OCS1), U11.17 (#OCS2), U11.19 (#OCS3), U11.21 (#OCS4)
unnamed: R56.P$1 (1), U11.22 (SDA/SMBDATA/NON_REM1)
unnamed: R52.P$2 (2), U11.28 (SUSP_IND/LOCAL_PWR/NON_REM0)
unnamed: Q2.3 (D), Q3.1 (G), R46.P$1 (1)
USB1_DN1_D_N: J21.2, U11.1 (USBDM_DN1)
USB1_DN1_D_P: J21.3, U11.2 (USBDP_DN1)
USB1_DN2_D_N: U11.3 (USBDM_DN2); also elsewhere on the board
USB1_DN2_D_P: U11.4 (USBDP_DN2); also elsewhere on the board
USB1_DN3_D_N: U11.6 (USBDM_DN3); also elsewhere on the board
USB1_DN3_D_P: U11.7 (USBDP_DN3); also elsewhere on the board
USB1_DN4_D_N: U11.8 (USBDM_DN4); also elsewhere on the board
USB1_DN4_D_P: U11.9 (USBDP_DN4); also elsewhere on the board
USB_#RESET: C40.P$2 (2), Q3.3 (D), R48.P$1 (1), U11.26 (#RESET); also elsewhere on the board
USB_RESET_OFF: Q2.1 (G); also elsewhere on the board

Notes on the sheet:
#SEL => HSD1; SEL => HSD2
NC: Int. Rpd
Select Defailt Config: * Self-powered * Strap options * Individual power/OCS
NON_REM[1:0] = b11 means Ports 1,2,3 are non-removable
Top-level USB hub
Power from the micro-USB jack steers the CM3's USB lines to the micro jack. When absent, the rest of the board is connected.
R-Pi Basestation USB network
CTT-20190123S
To second level hub
Low (and CM3 reset) puts hubs into reset.
Jumper Positions: 1-2 = USB Boot Enabled 2-3 = USB Boot Disabled
Micro-B for programming.
Spare port, general purpose.
Note the _N and _P suffixes are needed for Eagle to recognize the nets as diff'l.

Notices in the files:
CTT-20190123.brd:
COPYRIGHT 2019
